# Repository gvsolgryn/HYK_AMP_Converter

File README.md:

# HYK_AMP_Converter — DUDU7 → Hyundai i40 순정 AMP S/PDIF 변환기 (Rev.1)

Android 헤드유닛(DUDU7 / FYT7862)의 RCA Coaxial S/PDIF 출력을 현대 i40 순정 AMP(부품번호 `96370-3Z101`)의 차동 SPDIF 입력(`SPDIF+ / SPDIF− / GND`)에 연결하는 **능동 물리계층 변환기**입니다.
S/PDIF 프로토콜은 디코딩하지 않고, 75Ω 동축 신호를 정형해 순정 AMP가 기대하는 차동 신호로 바꿉니다.

> ⚠️ **제작 승인(Production Release) 문서가 아닙니다.**
> 회로·부품·핀 검증과 차량 시험이 끝나기 전에는 Gerber 발주와 부품 주문을 하지 마세요.
> 모든 설계 판단의 기준은 **`docs/DUDU7_i40_SPDIF_TX_Rev1_BOM_for_KiCad_Agent.md` (Rev.1, 2026-11-11)** 입니다.
> Rev.A2 문서의 LMR16006 Buck 전원단은 Rev.1에서 **사용하지 않습니다**.

## 현재 상태 (2026-11-16)

- 회로도: Rev.1 부품 **56개 배치·배선 완료**, **ERC 0건**, 넷리스트 핀 단위 대조 일치
- 커넥터 핀 배정 (GND는 항상 마지막): J3 `1=ACC_IN, 2=GND` · J2 `1=SPDIF−, 2=SPDIF+, 3=GND` (결정 로그 #23: FL1 출력과 일직선 배선)
- PCB: 배치·배선 완료, DRC 0 · 회로도 불일치 0, 3D 간섭 확인 완료. **사용자 승인으로 Gerber 생성·JLCPCB 주문 진행** (2026-11-16)
- 부품: 디바이스마트 장바구니·알리 목록 확정, **결제 보류** — 전원부 필터 시험 결과에 따라 진행 여부 결정 (인계 문서 §5.2, 결정 로그 #26)
- 확정 결정 기록: BOM 문서 §9 "Decision log"

## 설계 개요

```text
ACC 12V ─ J3 ─ F1 2A ─┬─ ACC_FUSED ─ D1 SB360 ─┬─ VIN_PROTECTED ─ U1 TSR 1-2450 ─ +5V ─ U2 TPS7B8333 ─ +3.3V
                      └─ D2 TVS (GND)         └─ C1 / C2 (GND)

J1 BNC 75Ω ─ R1 75Ω 종단 ─ C9 AC 결합 ─ U3 TLV3601 (IN− = VREF 1.65V) ─ R5 ─ U4 MAX3295
U4 Y ─ R7 120Ω ─ R10 0Ω ─ FL1 1→4 ─┬─ SPDIF+ ─ J2
                                   R9 56Ω (CMC 뒤, 커넥터 쪽)
U4 Z ─ R8 120Ω ─ R11 0Ω ─ FL1 2→3 ─┴─ SPDIF− ─ J2
```

- 전원은 **ACC 12V만 사용**합니다. 상시 B+는 쓰지 않습니다 (차량 IBS 배터리 센서 학습 보호).
- 2-layer PCB, 부품은 전부 Top 실장, 일반 수동소자는 0805 (손납땜 기준).
- 외함: **케이스포유 RT-75 (RT-7511, 75 × 30.9 × 110 mm, 국산)** — 알루미늄 압출 본체(AL6061), 전·후면 판넬(AL5052), PCB 홈(1.6T). 결정 로그 #16 참고.
- 시험 샘플레이트: 우선 44.1 / 48 kHz. 192 kHz는 MAX3295 20 Mbps 한계로 보장하지 않습니다.

## 주요 부품

| Ref | 부품 | 패키지 | 역할 |
|---|---|---|---|
| U1 | TRACO **TSR 1-2450** | SIP-3 THT | 12V → 5V 스위칭 모듈 |
| U2 | TI **TPS7B8333QDCYRQ1** | SOT-223 (DCY) | 5V → 3.3V LDO — **8330/8350 아님** |
| U3 | TI **TLV3601QDBVRQ1** | SOT-23-5 | 고속 비교기 (S/PDIF 정형) |
| U4 | ADI **MAX3295AUT+T** | SOT-23-6 | 20 Mbps 차동 드라이버 |
| D1 | **SB360** (범용, DO-201AD) | DO-201 축형 | 직렬 역극성 보호 Schottky |
| D2 | Littelfuse **1.5KE22CA** | DO-201AE 축형 | 양방향 TVS (`ACC_FUSED`–GND 병렬, D1 앞) |
| F1 | Keystone **3557-2** 홀더 + Littelfuse **0891002.NXS** | THT | 2A LP Mini 블레이드 퓨즈 |
| FL1 | TDK **ACM2012-900-2P-T001** | 2012 SMD | 차동 출력 공통모드 초크 (후보) |
| J1 | Kinghelm **KH-BNC75-3511** | THT | 75Ω BNC 입력 |
| J2 | JST **S3B-XH-A(LF)(SN)** (+ XHP-3 / SXH-001T-P0.6) | THT 2.5mm | `SPDIF− / SPDIF+ / GND` 출력 (`-1` 변형 금지) |
| J3 | JST **B2PS-VH** (+ VHR-2N / SVH-21T-P1.1) | THT 3.96mm | `ACC 12V / GND` 입력 |

핀아웃은 `references/datasheets/`의 데이터시트 원문으로 대조했습니다. 상세 내용은 `AGENTS.md`의 "검증된 핀아웃"을 보세요.

## 실장 구성 (FIT / DNP)

| 구분 | 부품 | 기본 상태 | 비고 |
|---|---|---|---|
| 극성 선택 | R10 (Y→+), R11 (Z→−) | **FIT** | 순정 극성 |
| 극성 선택 | R12 (Y→−), R13 (Z→+) | DNP | 반전 시험 시 R10/R11 대신 실장. **4개 동시 실장 금지** (Y/Z 쇼트) |
| CMC 바이패스 | R14 (FL1 1↔4), R15 (FL1 2↔3) | DNP | FL1 제거 시에만 실장 |
| 히스테리시스 | R6 R_HYS | DNP, Value `TBD` | **0Ω 실장 금지** (비교기 래치) |
| EMI 커패시터 | C11~C14 | DNP, Value `TBD` | OEM C593/C433/C430/C431 대응 |
| 쉴드 접지 | R17 0Ω (J1 쉴드 `SHIELD` → GND) | **FIT** | 잡음·그라운드 루프 시 R17 제거 후 C15 실장 |
| 쉴드 접지 | C15 | DNP, Value `TBD` | R17 대신 쓰는 용량 결합 자리 |
| DE | R16 0Ω → +3.3V | **FIT** | 지연 enable 회로는 미설계 |

## 외함 (케이스포유 RT-75)

|항목|내용|
|---|---|
|모델|RT-7511: 전체 75 × 30.9 × 110 mm (본체 74.9 × 30.5 × 107, 판넬 1.5 mm). RT-7590(본체 87 mm)도 같은 단면|
|구매|[케이스포유](https://case4u.co.kr/product/detail.html?product_no=135) 직판 (24,200원, 부가세 포함), 디바이스마트 입점|
|PCB|내부 홈(1.6T, 홈 바닥 간 69.7 mm)에 끼움 → **PCB 외형 69.5 × 100.0 mm** (JLCPCB 특가 한도 102 mm, 결정 로그 #18). 앞 가장자리는 본체 앞끝, 뒤쪽 약 7 mm는 빈 공간. PCB 아래 4.5 mm, 위 약 19.4 mm|
|앞판|J1 BNC 나사부가 관통해 너트로 고정 (D형 Ø12.8 추정, 데이터시트 재확인). 결정 로그 #17|
|뒷판 (권장, 미확정)|하네스용 그로밋/PG7 글랜드 1개. J2·J3은 케이스 안쪽 PCB 위에 두고 판넬에 사각 구멍을 내지 않음|
|고정 (미확정)|플랜지 없음 → 벨크로·양면테이프 + 케이블타이, 또는 L브래킷|
|가공·마킹·실크|**PCB 배치 확정 → 시제품 조립으로 맞춤 확인 → 그 후** 직접 가공 또는 케이스포유에 구멍 가공·레이저 마킹·실크 인쇄 의뢰|

## 남은 일

- 부품 결제 (보류 중) → 기판·부품 도착 후 실물 맞춤(J1 축 높이 실측) → 조립 → 시험
- 뒷판 하네스 출구, 케이스 고정 방법, 판넬 가공 (시제품 맞춤 확인 후)
- 구매 후 회로도 `Manufacturer`·`MPN` 필드 기입 (결정 로그 #26 품번)

케이스 접지: J1 나사부 → 톱니 와셔로 앞판(케이스)과 연결, 케이스는 차체와 절연, 회로 쪽은 `SHIELD` → R17(0Ω) → GND (결정 로그 #25).

미완료 검증: DUDU7 실측 전압, AMP 쪽 종단·입력 레벨, OEM F400 대비 CMC 적합성, 실차 팝노이즈(DE), 무입력 발진(R_HYS).

PCB 작업 인계: [`docs/DUDU7_i40_SPDIF_TX_Rev1_PCB_Mechanical_Handoff_20261113.md`](docs/DUDU7_i40_SPDIF_TX_Rev1_PCB_Mechanical_Handoff_20261113.md)

## 폴더 구조

```
HYK_AMP_Converter/
├─ HYK_AMP_Converter.kicad_pro / .kicad_sch / .kicad_pcb   ← KiCad 10 프로젝트
├─ sym-lib-table / fp-lib-table      ← 프로젝트 라이브러리 등록 (깃 관리 대상)
├─ libraries/
│  ├─ symbols/      ← 3557-2, ACM2012H-900-2P-T00, MAX3295AUT-V-T, SB360_diode,
│  │                   TLV3601QDBVRQ1, TPS7B8350QDCYRQ1, TSR_1-2450
│  └─ footprints/   ← 위 부품의 .pretty (U2·U3·U4는 손납용 -L 변종 사용)
├─ docs/
│  ├─ DUDU7_i40_SPDIF_TX_Rev1_BOM_for_KiCad_Agent.md               ← ★ 최우선 사양 + Decision log
│  ├─ DUDU7_i40_SPDIF_TX_Rev1_PCB_Mechanical_Handoff_20261113.md   ← ★ PCB·외함 인계 (다음 작업 시작점)
│  ├─ DUDU7_i40_SPDIF_TX_Rev1_Schematic_Placement_and_Wiring.md/.html  ← 배치·배선 가이드
│  └─ archive/                                                      ← 지난 문서(Rev.A·Rev.A2·초기 감사). 이력용, 평소엔 읽지 않음
├─ references/datasheets/   ← 핀아웃 검증용 제조사 데이터시트 원문
├─ references/case_file/    ← 케이스포유 RT-75 도면 zip (로컬 전용, .gitignore — 저작권). 원본: [케이스포유 자료실 RT-75](https://www.case4u.co.kr/board/free/read.html?no=1060&board_no=7)
├─ AGENTS.md                ← AI 에이전트 작업 지침 (핀아웃·회로 규칙·사고 이력)
└─ .gitignore
```

## 시작하기

1. KiCad **10.0 이상**을 설치합니다 (작업 환경: 10.0.8).
2. 이 저장소를 클론합니다.
3. `HYK_AMP_Converter.kicad_pro`를 엽니다. 라이브러리가 프로젝트에 내장되어 있어(`sym-lib-table` / `fp-lib-table`) 추가 설정 없이 바로 쓸 수 있습니다.

## MCP 자동화 (선택)

서버는 [mixelpixx/KiCAD-MCP-Server](https://github.com/mixelpixx/KiCAD-MCP-Server) (v2.9.0, MIT)를 씁니다. 저장소 밖에 설치하고, 클라이언트 설정 파일은 이 저장소에 두지 않습니다 (경로가 PC마다 다름).

- 필요 도구: KiCad 10 (내장 Python 3.11 + `pcbnew`), Node.js 18 이상, Git
- 설치 (Windows PowerShell):

  ```powershell
  git clone --branch stable https://github.com/mixelpixx/KiCAD-MCP-Server.git $HOME\MCP\KiCAD-MCP-Server
  cd $HOME\MCP\KiCAD-MCP-Server
  .\setup-windows.ps1   # npm install + KiCad Python에 pip 의존성 설치 + 빌드 + windows-mcp-config.json 생성
  ```

  업데이트: 같은 폴더에서 `git pull` → `npm install` → `npm run build`
- 클라이언트 등록 (stdio). 생성된 `windows-mcp-config.json`을 기준으로 하되 `KICAD_MCP_OPERATING_MODE`를 추가합니다.

  ```json
  "kicad": {
    "command": "C:\\Program Files\\nodejs\\node.exe",
    "args": ["C:\\Users\\<USER>\\MCP\\KiCAD-MCP-Server\\dist\\index.js"],
    "env": {
      "PYTHONPATH": "C:\\Program Files\\KiCad\\10.0\\bin\\Lib\\site-packages",
      "KICAD_PYTHON": "C:\\Program Files\\KiCad\\10.0\\bin\\python.exe",
      "LOG_LEVEL": "info",
      "KICAD_MCP_OPERATING_MODE": "readonly"
    }
  }
  ```

  위치: omp `~/.omp/agent/mcp.json`, Claude Code `claude mcp add --scope user kicad --env ... -- node <dist\index.js>`, Claude Desktop `%APPDATA%\Claude\claude_desktop_config.json`
- 운용 모드 (`KICAD_MCP_OPERATING_MODE`)

  |값|도구 수 (v2.9.0 실측)|용도|
  |---|---:|---|
  |`readonly`|86|**기본값으로 사용.** 리뷰·ERC·넷리스트|
  |`manufacturing`|—|readonly + Gerber·BOM 등 출력. 사용자 승인 전 사용 금지|
  |`write` (또는 미설정)|250|회로도·PCB 편집. 작업할 때만 잠깐 전환|

  > ⚠️ 이 서버는 변수를 **설정하지 않으면 `write`(전체 쓰기)** 로 시작합니다. 반드시 `readonly`를 명시하세요.
- 도구가 많아 컨텍스트를 많이 씁니다. 줄이려면 `KICAD_MCP_TOOLBOXES=core`(또는 `schematic,drc` 등)를 추가합니다.
- PCB 실시간 연동(IPC)을 쓰려면 KiCad **Preferences → Plugins → Enable KiCad API**를 켜고 KiCad 창을 하나만 엽니다.
- KiCad 10은 회로도 IPC가 없습니다. MCP의 회로도 쓰기는 `.kicad_sch` 파일을 **직접 덮어쓰므로** 다음 순서를 지키세요.
  1. GUI에서 저장하고 회로도 편집기를 닫습니다.
  2. `backup/`에 백업합니다.
  3. 요청한 범위만 수정합니다.
  4. diff를 확인합니다.

  자세한 내용은 `AGENTS.md`에 있습니다.

## 라이선스

[The Unlicense](LICENSE) (퍼블릭 도메인)

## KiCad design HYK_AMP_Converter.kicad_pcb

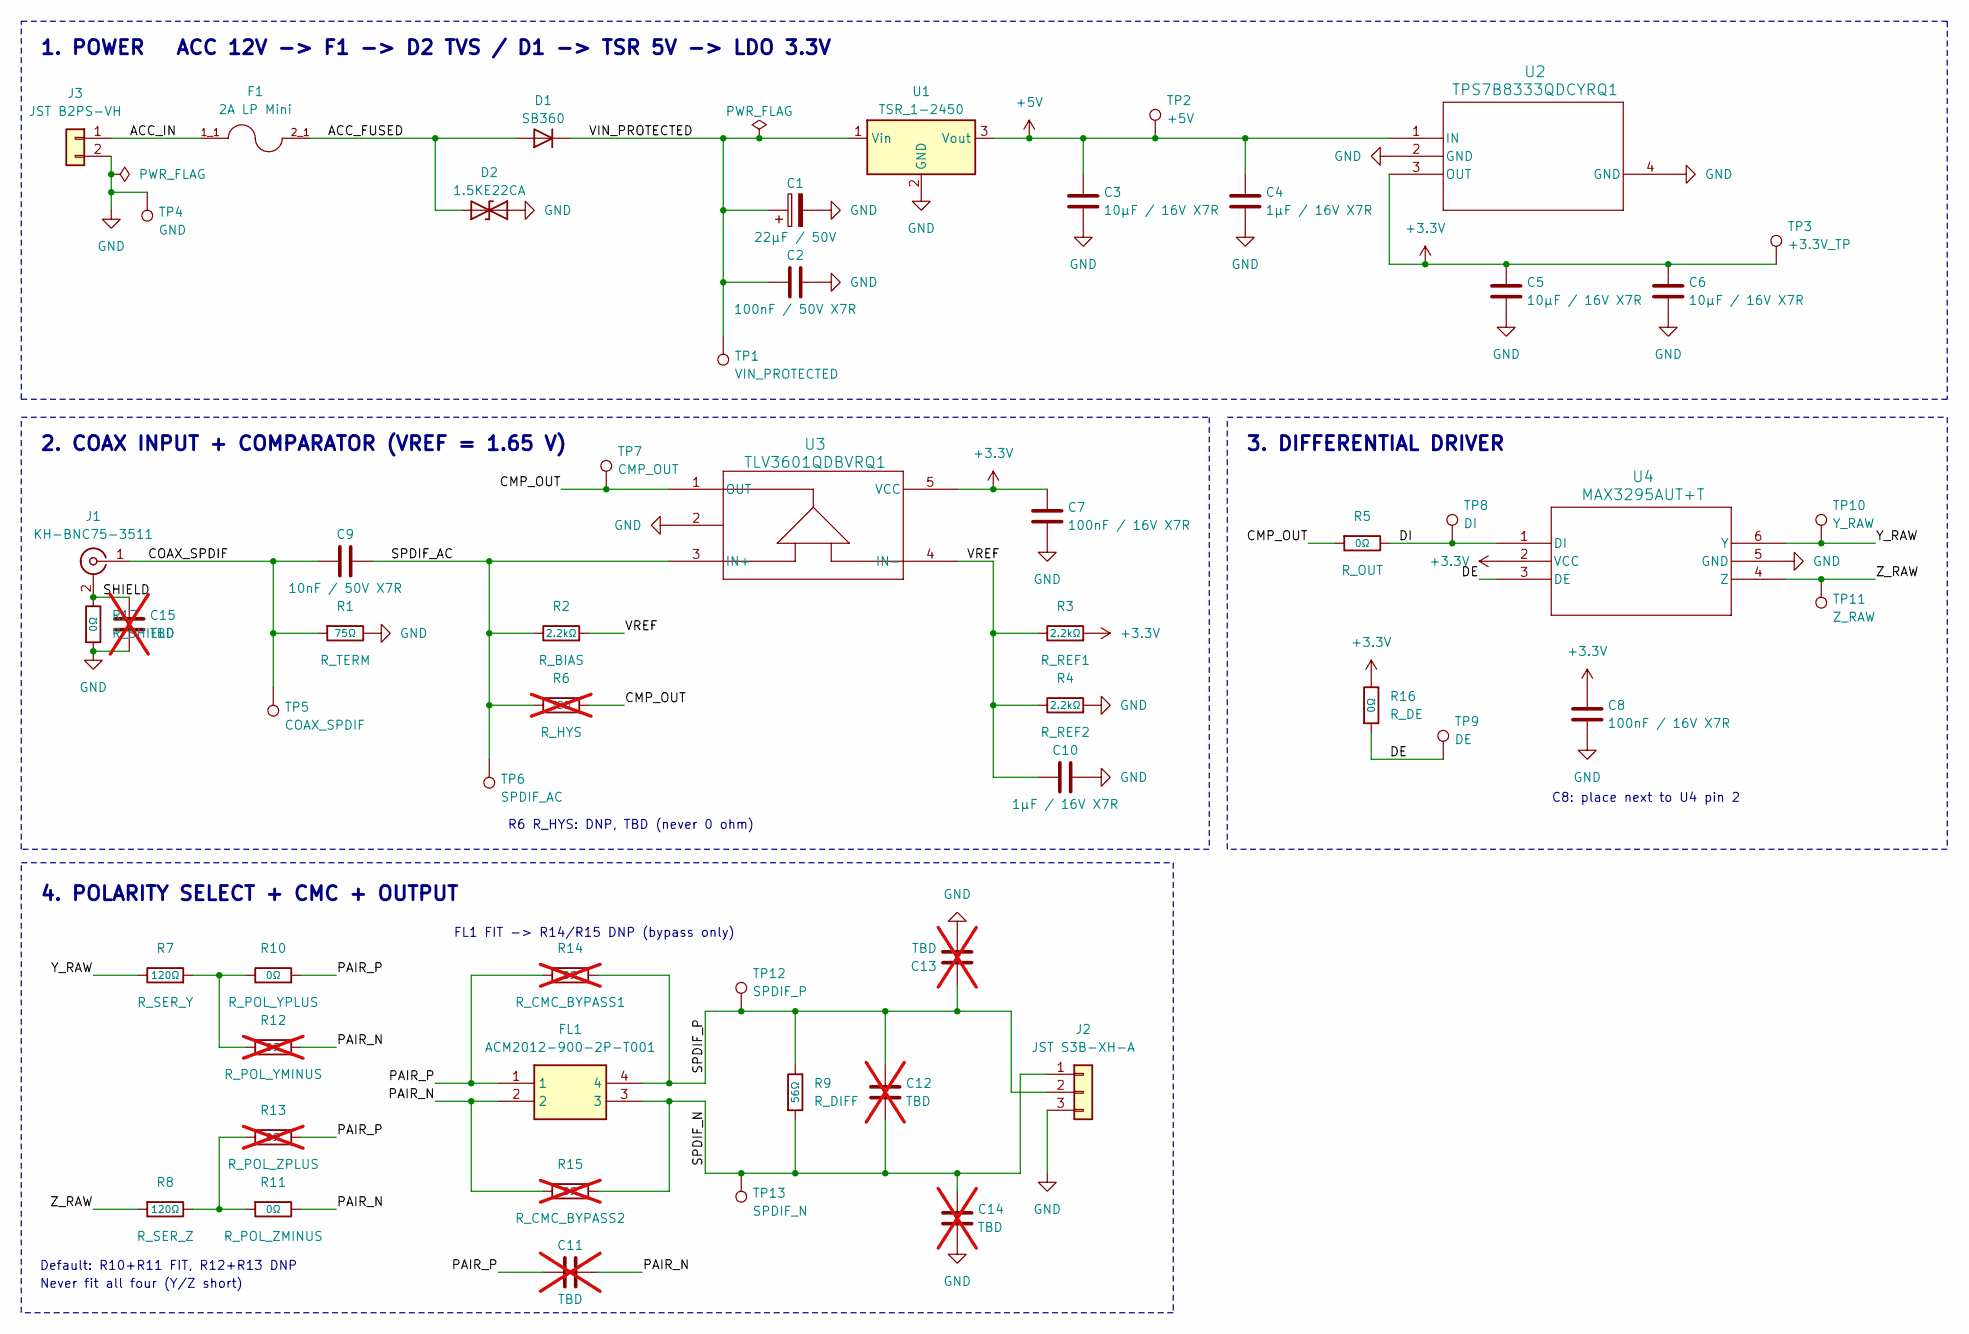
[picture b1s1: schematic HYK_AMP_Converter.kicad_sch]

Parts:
C1: 22µF / 50V; CP_Radial_D5.0mm_P2.00mm; MPN EEU-FR1H220
C2: 100nF / 50V X7R; C_0805_2012Metric_Pad1.18x1.45mm_HandSolder
C3, C5, C6: 10µF / 16V X7R; C_0805_2012Metric_Pad1.18x1.45mm_HandSolder
C4, C10: 1µF / 16V X7R; C_0805_2012Metric_Pad1.18x1.45mm_HandSolder
C7, C8: 100nF / 16V X7R; C_0805_2012Metric_Pad1.18x1.45mm_HandSolder
C9: 10nF / 50V X7R; C_0805_2012Metric_Pad1.18x1.45mm_HandSolder
C11, C12, C13, C14, C15: TBD; C_0805_2012Metric_Pad1.18x1.45mm_HandSolder; not fitted
D1: SB360; P2_DO-201
D2: 1.5KE22CA; D_DO-201AE_P15.24mm_Horizontal
F1: 2A LP Mini; FUSE_3557-2; MPN 3557-2
FL1: ACM2012-900-2P-T001; ACM20121022PT001; MPN ACM2012-900-2P-T001
J1: KH-BNC75-3511
J2: JST S3B-XH-A; JST_XH_S3B-XH-A_1x03_P2.50mm_Horizontal_Drill1.0
J3: JST B2PS-VH; JST_VH_B2PS-VH_1x02_P3.96mm_Horizontal
R1: 75Ω; R_0805_2012Metric_Pad1.20x1.40mm_HandSolder
R2, R3, R4: 2.2kΩ; R_0805_2012Metric_Pad1.20x1.40mm_HandSolder
R5, R10, R11, R16, R17: 0Ω; R_0805_2012Metric_Pad1.20x1.40mm_HandSolder
R6: TBD; R_0805_2012Metric_Pad1.20x1.40mm_HandSolder; not fitted
R7, R8: 120Ω; R_0805_2012Metric_Pad1.20x1.40mm_HandSolder
R9: 56Ω; R_0805_2012Metric_Pad1.20x1.40mm_HandSolder
R12, R13, R14, R15: 0Ω; R_0805_2012Metric_Pad1.20x1.40mm_HandSolder; not fitted
TP1: VIN_PROTECTED; TestPoint_Pad_D1.5mm
TP2: +5V; TestPoint_Pad_D1.5mm
TP3: +3.3V_TP; TestPoint_Pad_D1.5mm
TP4: GND; TestPoint_Pad_D1.5mm
TP5: COAX_SPDIF; TestPoint_Pad_D1.5mm
TP6: SPDIF_AC; TestPoint_Pad_D1.5mm
TP7: CMP_OUT; TestPoint_Pad_D1.5mm
TP8: DI; TestPoint_Pad_D1.5mm
TP9: DE; TestPoint_Pad_D1.5mm
TP10: Y_RAW; TestPoint_Pad_D1.5mm
TP11: Z_RAW; TestPoint_Pad_D1.5mm
TP12: SPDIF_P; TestPoint_Pad_D1.5mm
TP13: SPDIF_N; TestPoint_Pad_D1.5mm
U1: TSR_1-2450; Converter_DCDC_TRACO_TSR-1_THT
U2: TPS7B8333QDCYRQ1; SOT_8350QDCYRQ1_TEX-L
U3: TLV3601QDBVRQ1; SOT_DBVRQ1_TEX-L
U4: MAX3295AUT+T; 21-0058_U6CN-2_MXM-L

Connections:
+3.3V: C5.1, C6.1, C7.2, C8.1, R3.2, R16.1, TP3.1 (1_1), U2.3 (OUT), U3.5 (VCC), U4.2 (VCC)
+5V: C3.1, C4.2, TP2.1 (1_1), U1.3 (Vout), U2.1 (IN)
/ACC_FUSED: D1.2 (A), D2.1 (A1), F1.2_1, F1.2_2
/ACC_IN: F1.1_1, F1.1_2, J3.1
/CMP_OUT: R5.2, R6.2, TP7.1 (1_1), U3.1 (OUT)
/COAX_SPDIF: C9.2, J1.1 (In), R1.2, TP5.1 (1_1)
/DE: R16.2, TP9.1 (1_1), U4.3 (DE)
/DI: R5.1, TP8.1 (1_1), U4.1 (DI)
/PAIR_N: C11.1, FL1.2, R11.1, R12.2, R15.1
/PAIR_P: C11.2, FL1.1, R10.2, R13.2, R14.1
/SHIELD: C15.1, J1.2 (Ext), R17.1
/SPDIF_AC: C9.1, R2.1, R6.1, TP6.1 (1_1), U3.3 (IN+)
/SPDIF_N: C12.2, C14.1, FL1.3, J2.1, R9.2, R15.2, TP13.1 (1_1)
/SPDIF_P: C12.1, C13.1, FL1.4, J2.2, R9.1, R14.2, TP12.1 (1_1)
/VIN_PROTECTED: C1.1, C2.1, D1.1 (K), TP1.1 (1_1), U1.1 (Vin)
/VREF: C10.1, R2.2, R3.1, R4.1, U3.4 (IN-)
/Y_RAW: R7.1, TP10.1 (1_1), U4.6 (Y)
/Z_RAW: R8.2, TP11.1 (1_1), U4.4 (Z)
GND: C1.2, C2.2, C3.2, C4.1, C5.2, C6.2, C7.1, C8.2, C10.2, C13.2, C14.2, C15.2, D2.2 (A2), J2.3, J3.2, R1.1, R4.2, R17.2, TP4.1 (1_1), U1.2 (GND), U2.2 (GND), U2.4 (GND), U3.2, U4.5 (GND)
unnamed: R7.2, R10.1, R12.1
unnamed: R8.1, R11.2, R13.1

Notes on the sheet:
4. POLARITY SELECT + CMC + OUTPUT
2. COAX INPUT + COMPARATOR (VREF = 1.65 V)
3. DIFFERENTIAL DRIVER
R6 R_HYS: DNP, TBD (never 0 ohm)
Never fit all four (Y/Z short)
C8: place next to U4 pin 2
Default: R10+R11 FIT, R12+R13 DNP
1. POWER ACC 12V -> F1 -> D2 TVS / D1 -> TSR 5V -> LDO 3.3V
FL1 FIT -> R14/R15 DNP (bypass only)

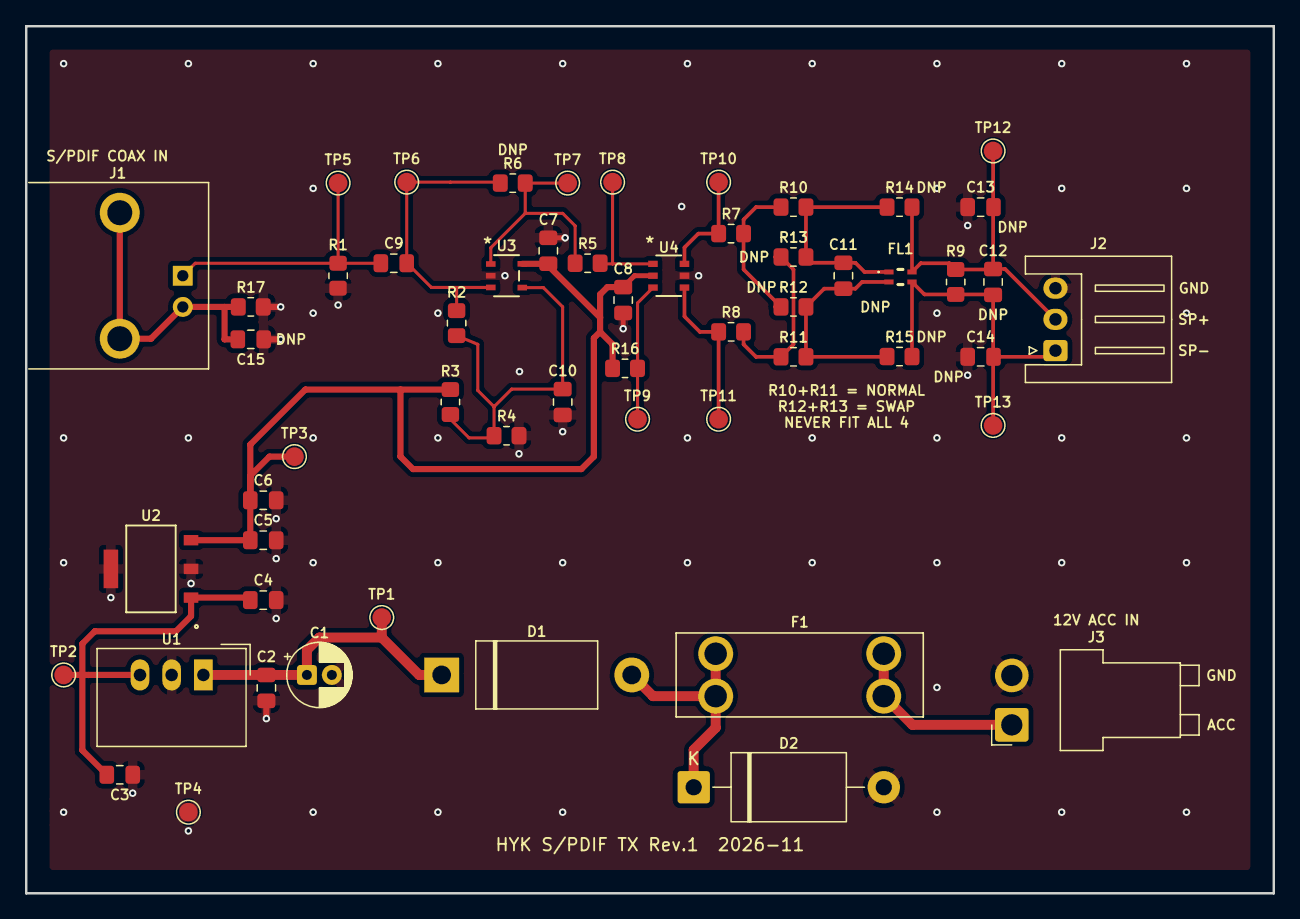
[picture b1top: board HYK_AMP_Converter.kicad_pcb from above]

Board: 2 copper layers, 100.0 x 69.5 mm, 57 parts (0 on the bottom side), 21 nets.

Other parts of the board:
MECH1: CASE_RT7511
